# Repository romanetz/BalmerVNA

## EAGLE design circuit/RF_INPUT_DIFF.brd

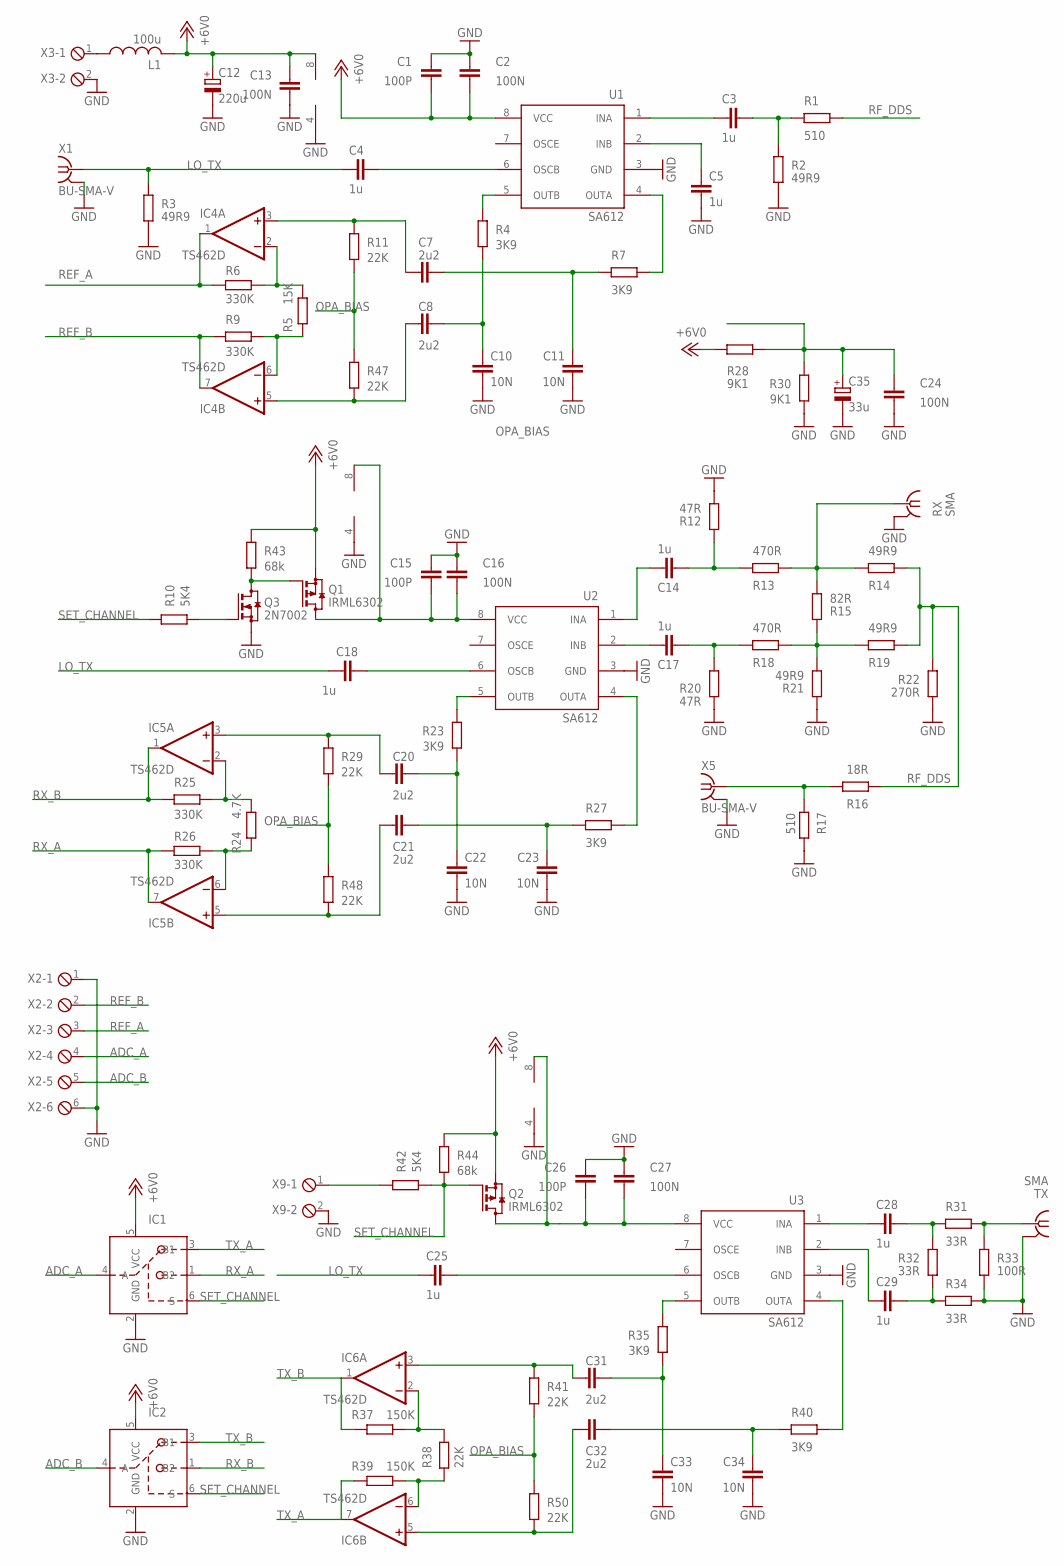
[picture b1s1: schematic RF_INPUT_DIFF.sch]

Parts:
C1, C15, C26: 100P; C0805
C2, C13, C16, C24, C27: 100N; C0603
C3, C5, C14, C17, C28, C29: 1u; C0603
C4, C18, C25: 1u; C0805
C7, C8, C20, C21, C31, C32: 2u2; C0805
C10, C11, C22, C23, C33, C34: 10N; C0805
C12: 220u; 153CLV-0605
C35: 33u; 153CLV-0605
IC1, IC2: SN74LVC1G3157DBVR; SOT23-6
IC4, IC5, IC6: TS462D; SO08
L1: 100u; 0207/12
Q1, Q2: IRML6302; SOT23
Q3: 2N7002; SOT23
R1, R17: 510; R0603
R2, R3, R14, R19, R21: 49R9; R0805
R4, R7, R23, R27, R35, R40: 3K9; R0603
R5: 15K; R0603
R6, R9, R25, R26: 330K; R0603
R10, R42: 5K4; R0603
R11, R29, R38, R41, R47, R48, R50: 22K; R0603
R12, R20: 47R; R0603
R13, R18: 470R; R0603
R15: 82R; R0603
R16: 18R; R0603
R22: 270R; R0603
R24: 4.7K; R0603
R28, R30: 9K1; R0603
R31, R32, R34: 33R; R0603
R33: 100R; R0603
R37, R39: 150K; R0603
R43, R44: 68k; R0603
RX: SMA; J502-ND-142-0701-801/806
TX: SMA; J502-ND-142-0701-801/806
U1, U2, U3: SA612; SO8
X1, X5: BU-SMA-V
X2: MPT6; 6POL254
X3, X9: MPT2; 2POL254

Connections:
+6V0: C1.1, C2.1, C12.+, C13.1, IC1.5 (VCC), IC2.5 (VCC), IC4.8 (V+), L1.2, Q1.2 (S), Q2.2 (S), R28.2, R43.1, R44.1, U1.8 (VCC)
ADC_A: IC1.4 (A), X2.4
ADC_B: IC2.4 (A), X2.5
GND: C1.2, C2.2, C5.2, C10.2, C11.2, C12.-, C13.2, C15.2, C16.2, C22.2, C23.2, C24.1, C26.2, C27.2, C33.2, C34.2, C35.-, IC1.2 (GND), IC2.2 (GND), IC4.4 (V-), IC5.4 (V-), IC6.4 (V-), Q3.2 (S), R2.1, R3.2, R12.2, R17.2, R20.1, R21.1, R22.2, R30.2, R33.2, R34.1, RX.G@1 (2), RX.G@2 (2), RX.G@3 (2), RX.G@4 (2), TX.G@1 (2), TX.G@2 (2), TX.G@3 (2), TX.G@4 (2), U1.3 (GND), U2.3 (GND), U3.3 (GND), X1.2, X1.3 (2), X1.4 (2), X1.5 (2), X2.1, X2.6, X3.2, X5.2, X5.3 (2), X5.4 (2), X5.5 (2), X9.2
LO_TX: C4.1, C18.1, C25.1, R3.1, X1.1
unnamed: R15.1, R18.1, R19.2, R21.2
unnamed: IC6.2 (-IN), R37.1, R38.1
unnamed: C25.2, U3.6 (OSCB)
unnamed: C26.1, C27.1, IC6.8 (V+), Q2.3 (D), U3.8 (VCC)
unnamed: R13.1, R14.2, R15.2, RX.1
unnamed: Q1.1 (G), Q3.3 (D), R43.2
unnamed: L1.1, X3.1
unnamed: C15.1, C16.1, IC5.8 (V+), Q1.3 (D), U2.8 (VCC)
unnamed: R42.1, X9.1
unnamed: IC4.2 (-IN), R5.1, R6.1
unnamed: C31.1, IC6.3 (+IN), R41.1
unnamed: C32.1, IC6.5 (+IN), R50.2
unnamed: IC4.6 (-IN), R5.2, R9.1
unnamed: Q3.1 (G), R10.2
unnamed: C7.1, IC4.3 (+IN), R11.1
unnamed: C8.1, IC4.5 (+IN), R47.2
unnamed: C20.1, IC5.3 (+IN), R29.1
unnamed: C21.1, IC5.5 (+IN), R48.2
unnamed: IC5.6 (-IN), R24.2, R26.1
unnamed: IC5.2 (-IN), R24.1, R25.1
unnamed: IC6.6 (-IN), R38.2, R39.1
unnamed: R31.1, R33.1, TX.1
unnamed: C28.2, R31.2, R32.1
unnamed: C29.2, R32.2, R34.2
unnamed: C29.1, U3.2 (INB)
unnamed: C28.1, U3.1 (INA)
unnamed: C31.2, C33.1, R35.2
unnamed: R40.1, U3.4 (OUTA)
unnamed: C32.2, C34.1, R40.2
unnamed: R35.1, U3.5 (OUTB)
unnamed: C17.1, U2.2 (INB)
unnamed: C17.2, R18.2, R20.2
unnamed: C14.1, U2.1 (INA)
unnamed: C20.2, C22.1, R23.2
unnamed: R27.1, U2.4 (OUTA)
unnamed: C21.2, C23.1, R27.2
unnamed: R23.1, U2.5 (OUTB)
unnamed: C14.2, R12.1, R13.2
unnamed: C18.2, U2.6 (OSCB)
unnamed: C5.1, U1.2 (INB)
unnamed: R14.1, R16.2, R19.1, R22.1
unnamed: C3.1, U1.1 (INA)
unnamed: C8.2, C10.1, R4.2
unnamed: R7.1, U1.4 (OUTA)
unnamed: C7.2, C11.1, R7.2
unnamed: R4.1, U1.5 (OUTB)
unnamed: C3.2, R1.2, R2.2
unnamed: C4.2, U1.6 (OSCB)
OPA_BIAS: C24.2, C35.+, R11.2, R28.1, R29.2, R30.1, R41.2, R47.1, R48.1, R50.1
REF_A: IC4.1 (OUT), R6.2, X2.3
REF_B: IC4.7 (OUT), R9.2, X2.2
RF_DDS: R1.1, R16.1, R17.1, X5.1
RX_A: IC1.1 (B2), IC5.7 (OUT), R26.2
RX_B: IC2.1 (B2), IC5.1 (OUT), R25.2
SET_CHANNEL: IC1.6 (S), IC2.6 (S), Q2.1 (G), R10.1, R42.2, R44.2
TX_A: IC1.3 (B1), IC6.7 (OUT), R39.2
TX_B: IC2.3 (B1), IC6.1 (OUT), R37.2

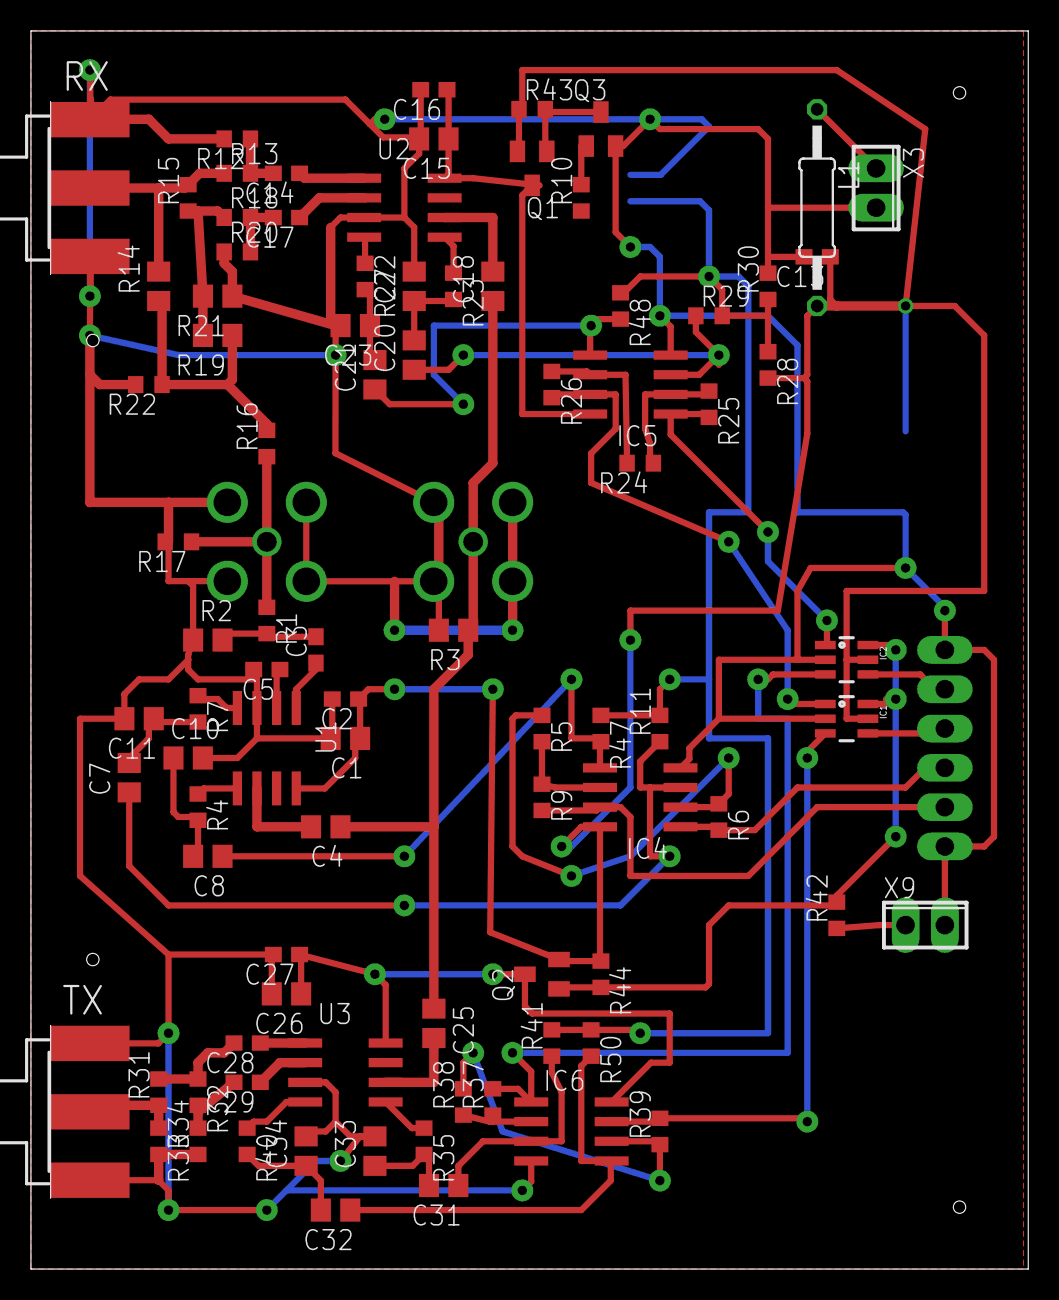
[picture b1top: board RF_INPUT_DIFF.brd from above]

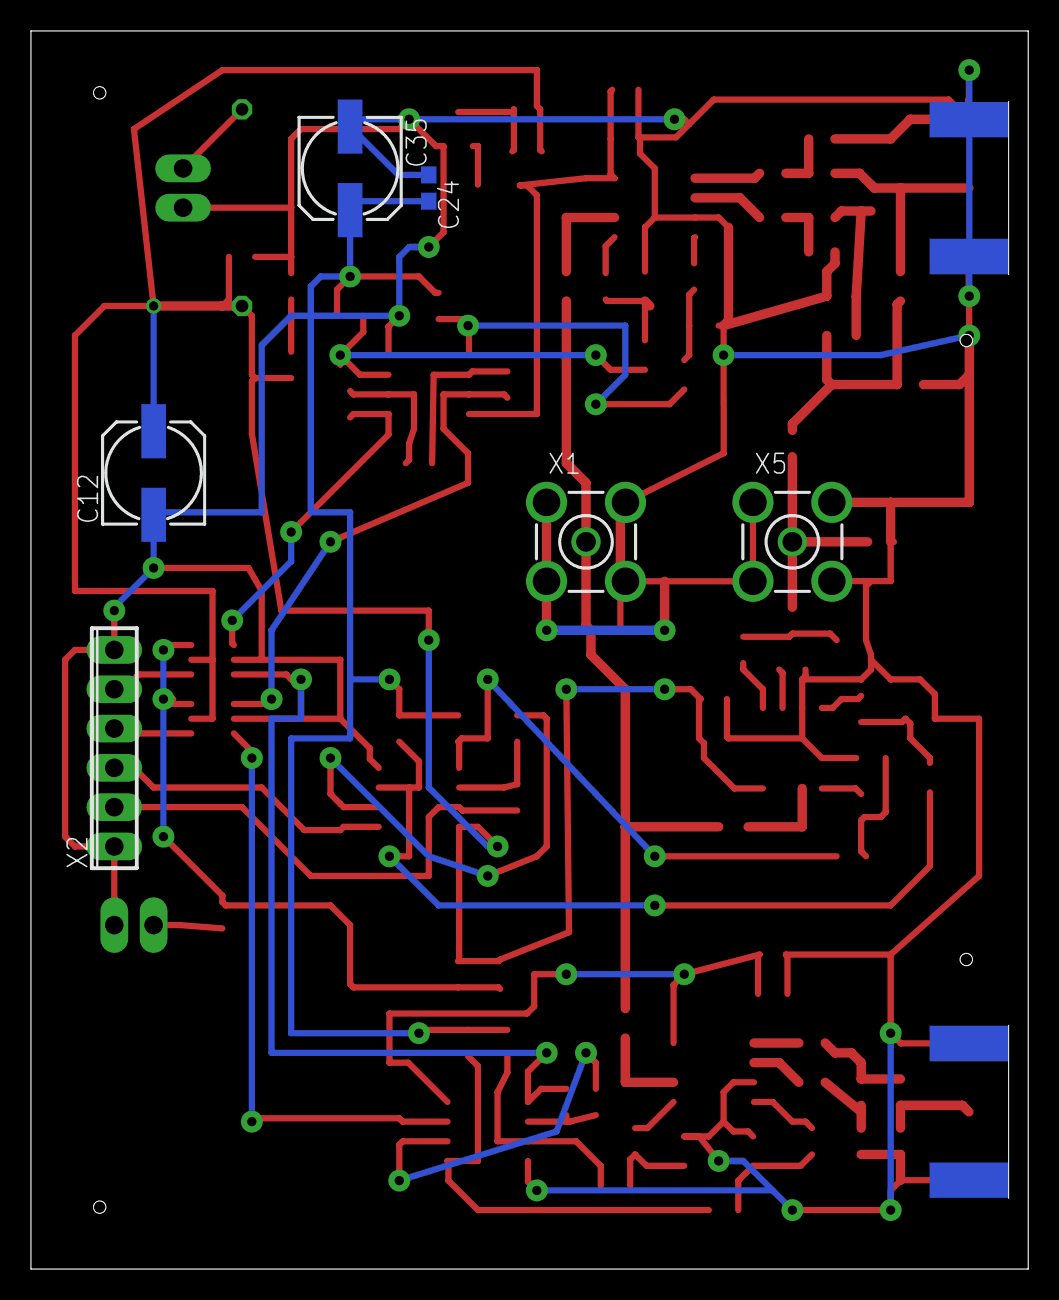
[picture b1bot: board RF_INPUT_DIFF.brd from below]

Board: 2 copper layers, 64.4 x 80.0 mm, 95 parts (6 on the bottom side), 62 nets.

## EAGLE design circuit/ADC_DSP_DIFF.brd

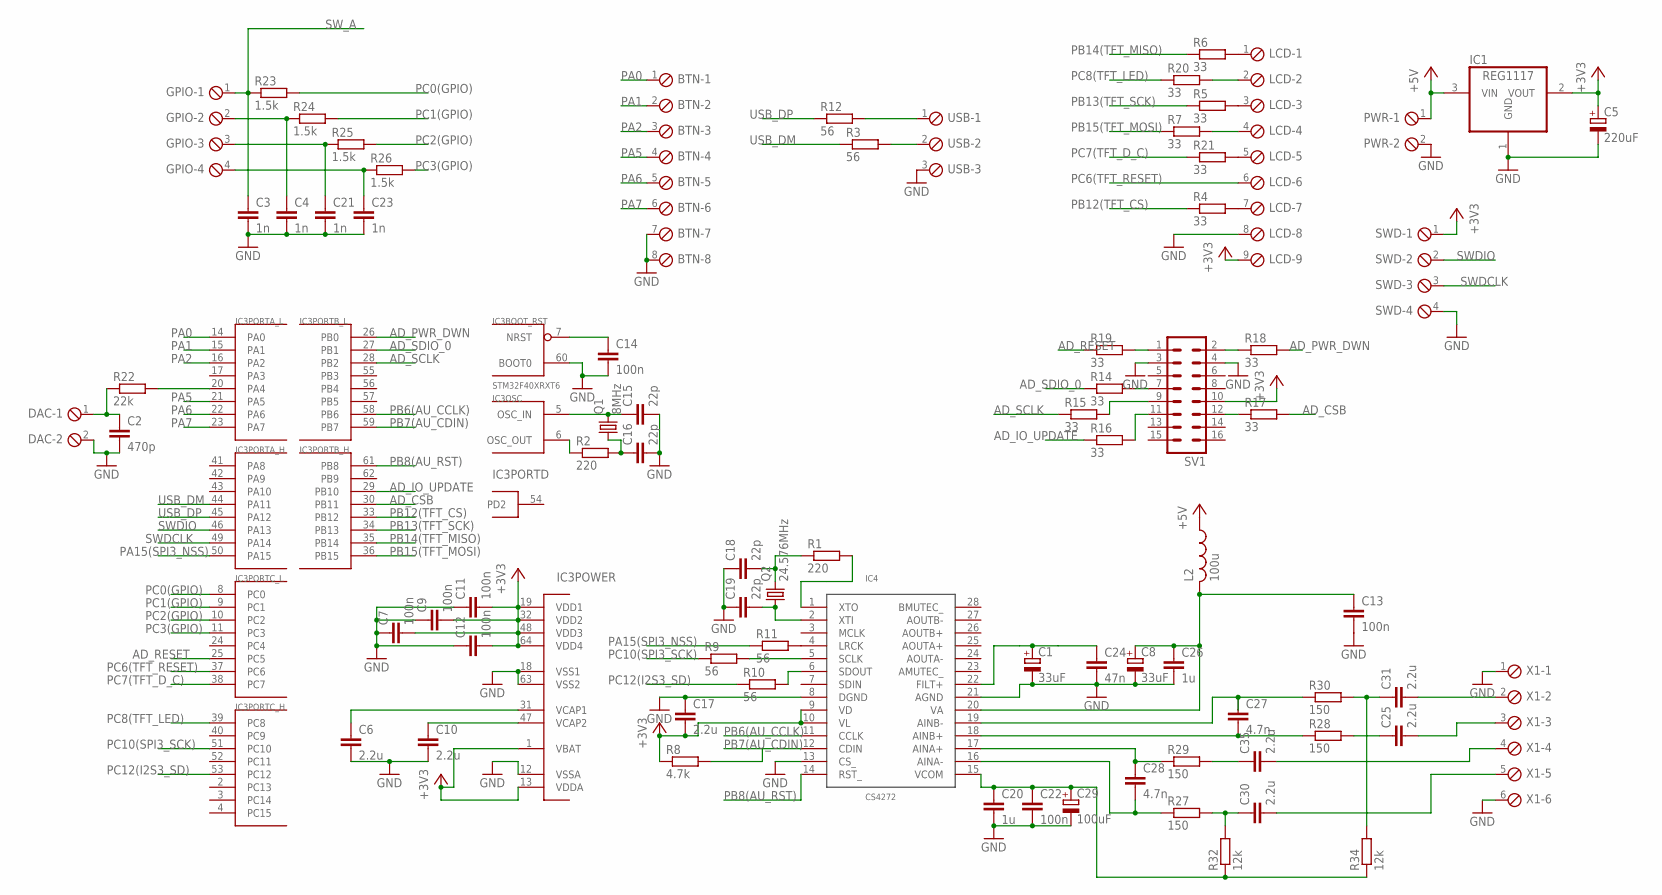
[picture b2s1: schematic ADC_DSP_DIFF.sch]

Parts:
BTN: MPT8; 8POL254
C1, C8: 33uF; 153CLV-0605
C2: 470p; C0805
C3, C4, C21, C23: 1n; C0805
C5: 220uF; 153CLV-0605
C6, C10, C17: 2.2u; C0603
C7, C9, C11, C12, C13, C14, C22: 100n; C0603
C15, C16, C18, C19: 22p; C0603
C20, C26: 1u; C0603
C24: 47n; C0805
C25, C30, C31, C35: 2.2u; C0805
C27, C28: 4.7n; C0805
C29: 100uF; 153CLV-0605
DAC: MPT2; 2POL254
GPIO: MPT4; 4POL254
IC1: REG1117; SOT223
IC3: STM32F40XRXT6; TQFP64
IC4: CS4272; TSSOP28
L2: 100u; 0207/12
LCD: MPT9; 9POL254
PWR: MPT2; 2POL254
Q1: 8MHz; HC49/S
Q2: 24.576MHz; HC49/S
R1, R2: 220; R0603
R3, R9, R10, R11, R12: 56; R0603
R4, R5, R6, R7, R14, R15, R16, R17, R18, R19, R20, R21: 33; R0603
R8: 4.7k; R0603
R22: 22k; R0603
R23, R24, R25, R26: 1.5k; R0603
R27, R28, R29, R30: 150; R0603
R32, R34: 12k; R0603
SV1: ML16
SWD: MPT4; 4POL254
USB: MPT3; 3POL254
X1: MPT6; 6POL254

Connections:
4052_B: C4.1, GPIO.2, R24.1
+3V3: C5.+, C7.2, C9.2, C11.2, C12.2, C17.2, IC1.2 (VOUT), IC3.1 (VBAT), IC3.13 (VDDA), IC3.19 (VDD1), IC3.32 (VDD2), IC3.48 (VDD3), IC3.64 (VDD4), IC4.9 (VD), IC4.10 (VL), LCD.9, R8.1, SV1.10, SWD.1
+5V: IC1.3 (VIN), L2.1, PWR.1
AD_CSB: IC3.30 (PB11), R17.2
AD_IO_UPDATE: IC3.29 (PB10), R16.1
AD_PWR_DWN: IC3.26 (PB0), R18.2
AD_RESET: IC3.25 (PC5), R19.1
AD_SCLK: IC3.28 (PB2), R15.1
AD_SDIO_0: IC3.27 (PB1), R14.1
AINB+: C27.2, IC4.18 (AINB+), R28.1
AVCC: C8.+, C13.1, C26.1, IC4.20 (VA), L2.2
D+: R12.2, USB.1
D-: R3.2, USB.2
GND: BTN.7, BTN.8, C1.-, C2.2, C3.2, C4.2, C5.-, C6.2, C7.1, C8.-, C9.1, C10.2, C11.1, C12.1, C13.2, C14.2, C15.2, C16.2, C17.1, C18.1, C19.1, C20.2, C21.2, C22.2, C23.2, C24.2, C26.2, C29.-, DAC.2, IC1.1 (GND), IC3.12 (VSSA), IC3.18 (VSS1), IC3.60 (BOOT0), IC3.63 (VSS2), IC4.8 (DGND), IC4.13 (CS_), IC4.21 (AGND), LCD.8, PWR.2, SV1.3, SV1.4, SWD.4, USB.3, X1.1, X1.6
unnamed: C10.1, IC3.47 (VCAP2)
unnamed: C6.1, IC3.31 (VCAP1)
unnamed: R16.2, SV1.11
unnamed: C14.1, IC3.7 (NRST)
unnamed: C15.1, IC3.5 (OSC_IN), Q1.2
unnamed: C16.1, Q1.1, R2.2
unnamed: C19.2, IC4.2 (XTI), Q2.1
unnamed: C18.2, Q2.2, R1.1
unnamed: IC4.4 (LRCK), R11.2
unnamed: IC4.5 (SCLK), R9.2
unnamed: IC4.6 (SDOUT), R10.2
unnamed: C1.+, C24.1, IC4.22 (FILT+)
unnamed: C27.1, IC4.19 (AINB-), R30.1
unnamed: R14.2, SV1.7
unnamed: C35.2, X1.4
unnamed: R19.2, SV1.1
unnamed: IC4.1 (XTO), R1.2
unnamed: C28.1, IC4.17 (AINA+), R29.1
unnamed: IC3.6 (OSC_OUT), R2.1
unnamed: LCD.1, R6.2
unnamed: LCD.3, R5.2
unnamed: LCD.2, R20.2
unnamed: R15.2, SV1.9
unnamed: LCD.4, R7.2
unnamed: C28.2, IC4.16 (AINA-), R27.1
unnamed: R18.1, SV1.2
unnamed: C31.1, R30.2, R34.2
unnamed: R17.1, SV1.12
unnamed: LCD.7, R4.2
unnamed: LCD.5, R21.2
unnamed: IC3.20 (PA4), R22.2
unnamed: C2.1, DAC.1, R22.1
unnamed: C30.1, R27.2, R32.2
unnamed: C25.1, R28.2
unnamed: C21.1, GPIO.3, R25.1
unnamed: C23.1, GPIO.4, R26.1
unnamed: C31.2, X1.2
unnamed: C35.1, R29.2
unnamed: C25.2, X1.3
unnamed: C30.2, X1.5
PA0: BTN.1, IC3.14 (PA0)
PA1: BTN.2, IC3.15 (PA1)
PA2: BTN.3, IC3.16 (PA2)
PA5: BTN.4, IC3.21 (PA5)
PA6: BTN.5, IC3.22 (PA6)
PA7: BTN.6, IC3.23 (PA7)
PA15(SPI3_NSS): IC3.50 (PA15), R11.1
PB6(AU_CCLK): IC3.58 (PB6), IC4.11 (CCLK)
PB7(AU_CDIN): IC3.59 (PB7), IC4.12 (CDIN), R8.2
PB8(AU_RST): IC3.61 (PB8), IC4.14 (RST_)
PB12(TFT_CS): IC3.33 (PB12), R4.1
PB13(TFT_SCK): IC3.34 (PB13), R5.1
PB14(TFT_MISO): IC3.35 (PB14), R6.1
PB15(TFT_MOSI): IC3.36 (PB15), R7.1
PC0(GPIO): IC3.8 (PC0), R23.2
PC1(GPIO): IC3.9 (PC1), R24.2
PC2(GPIO): IC3.10 (PC2), R25.2
PC3(GPIO): IC3.11 (PC3), R26.2
PC6(TFT_RESET): IC3.37 (PC6), LCD.6
PC7(TFT_D_C): IC3.38 (PC7), R21.1
PC8(TFT_LED): IC3.39 (PC8), R20.1
PC10(SPI3_SCK): IC3.51 (PC10), R9.1
PC12(I2S3_SD): IC3.53 (PC12), R10.1
SWDCLK: IC3.49 (PA14), SWD.3
SWDIO: IC3.46 (PA13), SWD.2
SW_A: C3.1, GPIO.1, R23.1
USB_DM: IC3.44 (PA11), R3.1
USB_DP: IC3.45 (PA12), R12.1
VCOM: C20.1, C22.1, C29.+, IC4.15 (VCOM), R32.1, R34.1

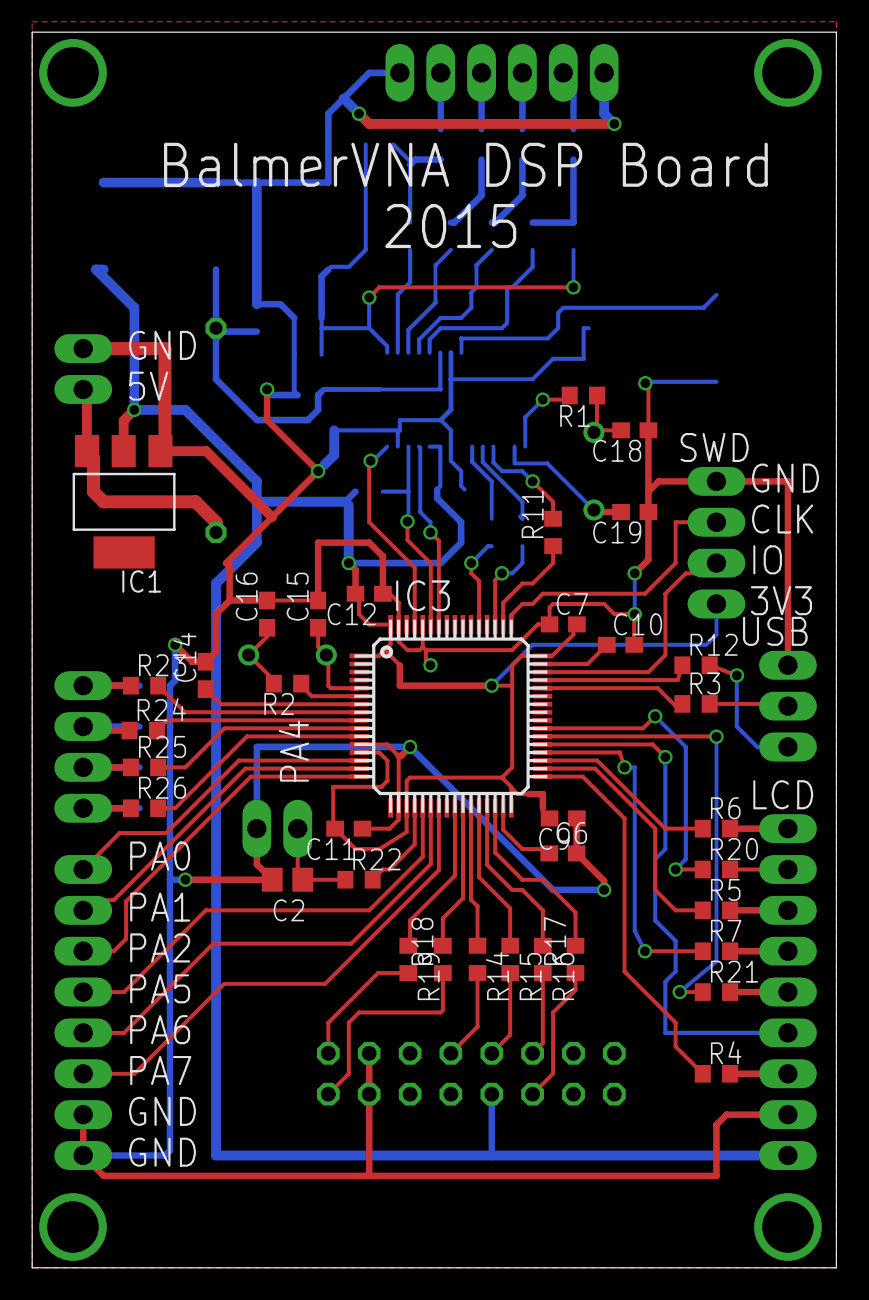
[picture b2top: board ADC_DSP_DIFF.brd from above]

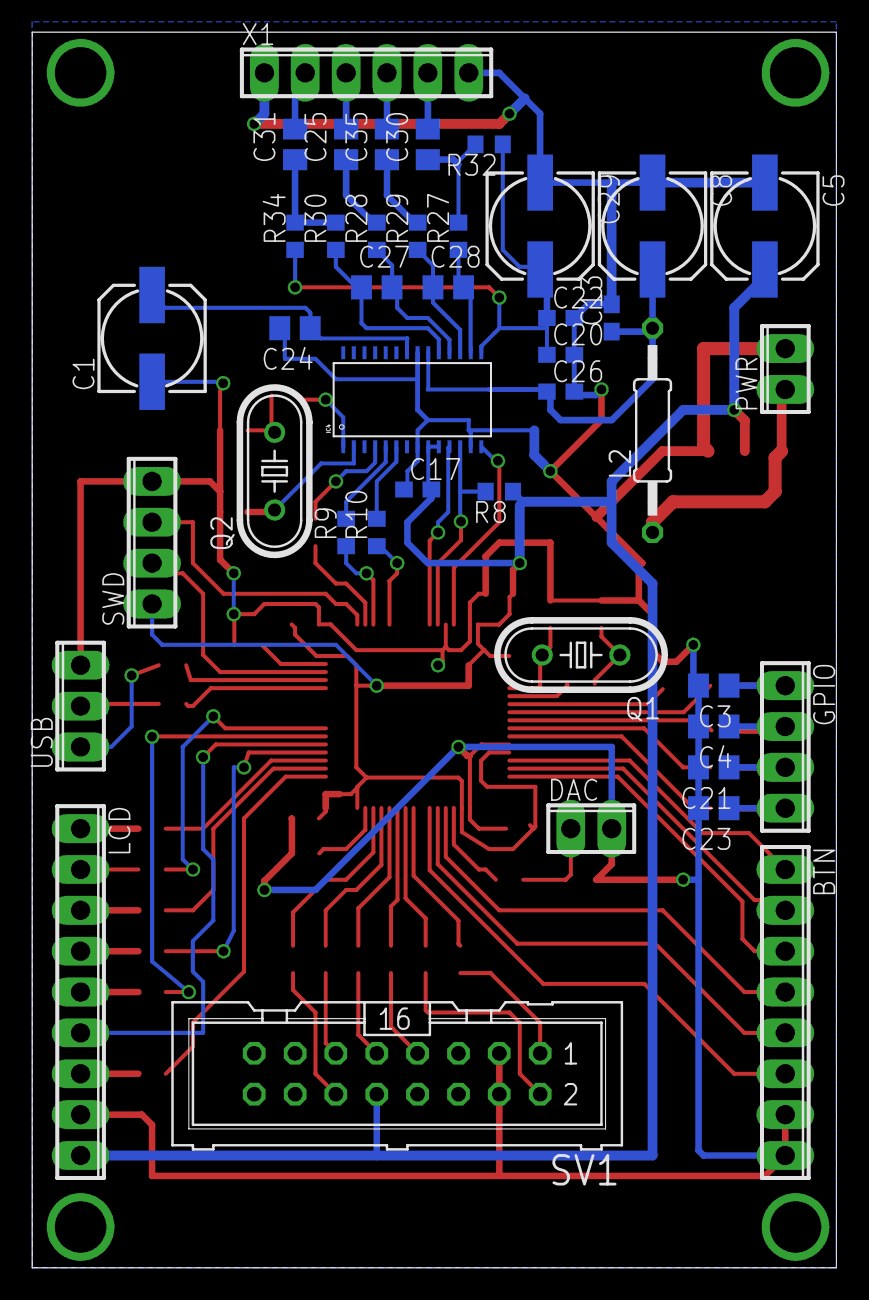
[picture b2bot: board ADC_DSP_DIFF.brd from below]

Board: 2 copper layers, 50.0 x 76.8 mm, 78 parts (42 on the bottom side), 83 nets.

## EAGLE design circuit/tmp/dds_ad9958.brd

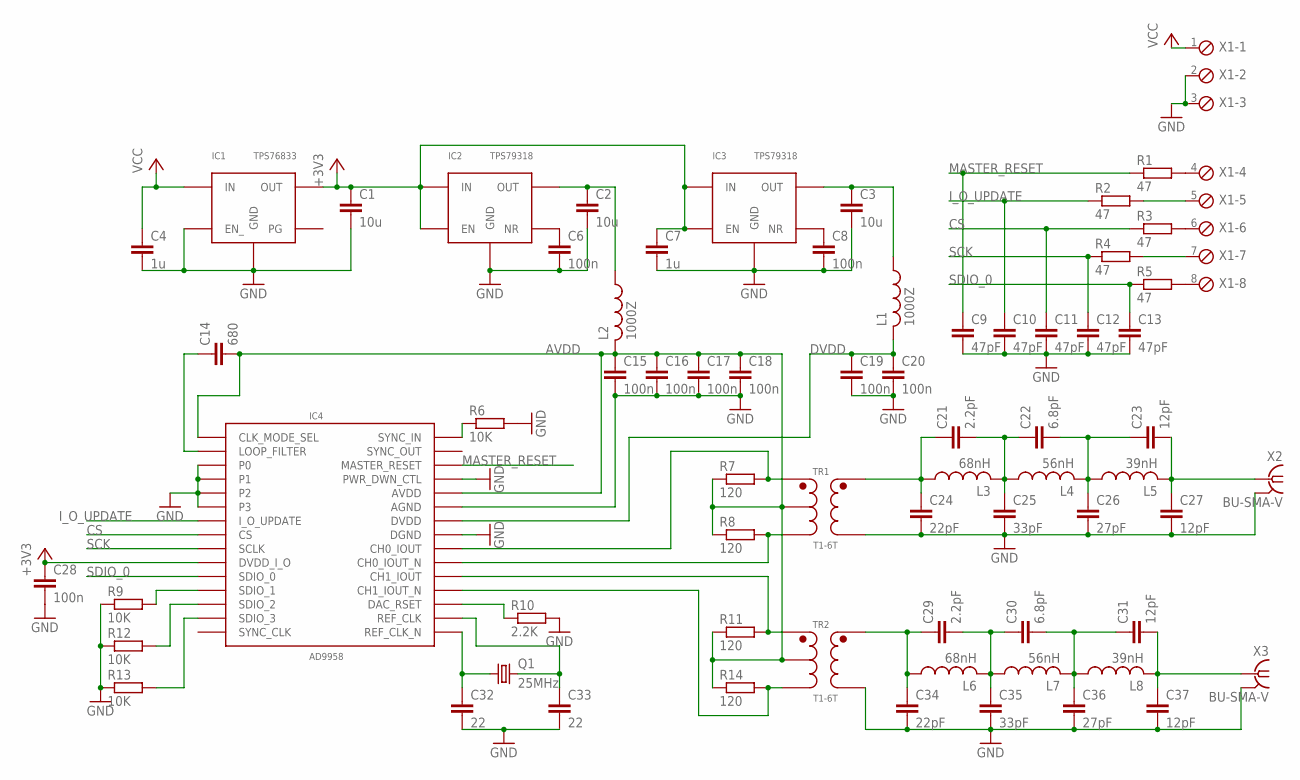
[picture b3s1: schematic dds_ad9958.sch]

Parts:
C1, C2, C3: 10u; C0805
C4, C7: 1u; C0603
C6, C8, C15, C16, C17, C18, C19, C20, C28: 100n; C0603
C9, C10, C11, C12, C13: 47pF; C0805
C14: 680; C0805
C21, C29: 2.2pF; C0805
C22, C30: 6.8pF; C0805
C23, C27, C31, C37: 12pF; C0805
C24, C34: 22pF; C0805
C25, C35: 33pF; C0805
C26, C36: 27pF; C0805
C32, C33: 22; C0603
IC1: TPS76833; SO8
IC2, IC3: TPS79318; SOT23-5
IC4: AD9958; CP-56-1
L1, L2: 1000Z; C0805
L3, L6: 68nH; C0805
L4, L7: 56nH; C0805
L5, L8: 39nH; C0805
Q1: 25MHz; HC49/S
R1, R2, R3, R4, R5: 47; R0603
R6, R9, R12, R13: 10K; R0603
R7, R8, R11, R14: 120; R0603
R10: 2.2K; R0603
TR1, TR2: T1-6T; KK81
X1: MPT8; 8POL254
X2, X3: BU-SMA-V

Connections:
+3V3: C1.1, C7.1, C28.1, IC1.5 (OUT), IC1.6 (OUT), IC2.1 (IN), IC2.3 (EN), IC3.1 (IN), IC3.3 (EN), IC4.P$49 (DVDD_I_O)
AVDD: C14.2, C15.1, C16.1, C17.1, C18.1, IC4.P$5 (AVDD), IC4.P$7 (AVDD), IC4.P$11 (AVDD), IC4.P$15 (AVDD), IC4.P$19 (AVDD), IC4.P$21 (AVDD), IC4.P$24 (CLK_MODE_SEL), IC4.P$26 (AVDD), IC4.P$29 (AVDD), IC4.P$30 (AVDD), IC4.P$31 (AVDD), IC4.P$33 (AVDD), IC4.P$35 (AVDD), IC4.P$36 (AVDD), IC4.P$37 (AVDD), IC4.P$39 (AVDD), L2.2, R7.1, R8.1, R11.1, R14.1, TR1.P$2 (SEC_CT), TR2.P$2 (SEC_CT)
CS: C11.1, IC4.P$47 (CS), R3.1
DVDD: C19.1, C20.1, IC4.P$45 (DVDD), IC4.P$55 (DVDD), L1.2
GND: C1.2, C2.2, C3.2, C4.2, C6.2, C7.2, C8.2, C9.2, C10.2, C11.2, C12.2, C13.2, C15.2, C16.2, C17.2, C18.2, C19.2, C20.2, C24.2, C25.2, C26.2, C27.2, C28.2, C32.2, C33.2, C34.2, C35.2, C36.2, C37.2, IC1.1 (GND), IC1.2 (EN_), IC2.2 (GND), IC3.2 (GND), IC4.P$4 (PWR_DWN_CTL), IC4.P$6 (AGND), IC4.P$10 (AGND), IC4.P$12 (AGND), IC4.P$16 (AGND), IC4.P$18 (AGND), IC4.P$20 (AGND), IC4.P$25 (AGND), IC4.P$40 (P0), IC4.P$41 (P1), IC4.P$42 (P2), IC4.P$43 (P3), IC4.P$44 (DGND), IC4.P$56 (DGND), IC4.PAD (AGND), R6.2, R9.1, R10.2, R12.1, R13.1, TR1.P$6 (PRI), TR2.P$6 (PRI), X1.2, X1.3, X2.2, X2.3 (2), X2.4 (2), X2.5 (2), X3.2, X3.3 (2), X3.4 (2), X3.5 (2)
I_O_UPDATE: C10.1, IC4.P$46 (I_O_UPDATE), R2.1
MASTER_RESET: C9.1, IC4.P$3 (MASTER_RESET), R1.1
unnamed: C32.1, IC4.P$22 (REF_CLK_N), Q1.1
unnamed: C21.1, C24.1, L3.1, TR1.P$4 (PRI_DOT)
unnamed: IC4.P$8 (CH0_IOUT), R7.2, TR1.P$3 (SEC_DOT)
unnamed: C6.1, IC2.4 (NR)
unnamed: C8.1, IC3.4 (NR)
unnamed: C2.1, IC2.5 (OUT), L2.1
unnamed: IC4.P$9 (CH0_IOUT_N), R8.2, TR1.P$1 (SEC)
unnamed: C3.1, IC3.5 (OUT), L1.1
unnamed: IC4.P$13 (CH1_IOUT), R11.2, TR2.P$3 (SEC_DOT)
unnamed: IC4.P$14 (CH1_IOUT_N), R14.2, TR2.P$1 (SEC)
unnamed: C21.2, C22.1, C25.1, L3.2, L4.1
unnamed: IC4.P$17 (DAC_RSET), R10.1
unnamed: IC4.P$1 (SYNC_IN), R6.1
unnamed: C14.1, IC4.P$27 (LOOP_FILTER)
unnamed: C33.1, IC4.P$23 (REF_CLK), Q1.2
unnamed: C22.2, C23.1, C26.1, L4.2, L5.1
unnamed: C23.2, C27.1, L5.2, X2.1
unnamed: C29.1, C34.1, L6.1, TR2.P$4 (PRI_DOT)
unnamed: C29.2, C30.1, C35.1, L6.2, L7.1
unnamed: C30.2, C31.1, C36.1, L7.2, L8.1
unnamed: C31.2, C37.1, L8.2, X3.1
unnamed: R3.2, X1.6
unnamed: R5.2, X1.8
unnamed: R1.2, X1.4
unnamed: R2.2, X1.5
unnamed: R4.2, X1.7
SCK: C12.1, IC4.P$48 (SCLK), R4.1
SDIO_0: C13.1, IC4.P$50 (SDIO_0), R5.1
SDIO_1: IC4.P$51 (SDIO_1), R9.2
SDIO_2: IC4.P$52 (SDIO_2), R12.2
SDIO_3: IC4.P$53 (SDIO_3), R13.2
VCC: C4.1, IC1.3 (IN), IC1.4 (IN), X1.1

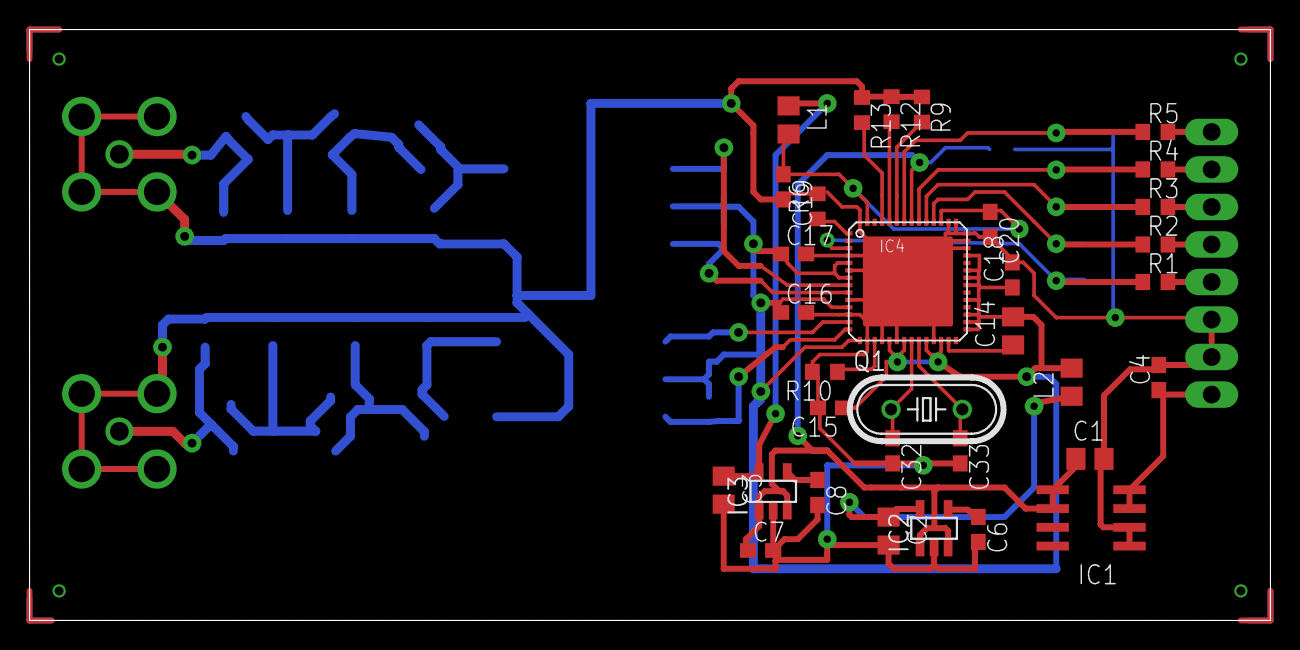
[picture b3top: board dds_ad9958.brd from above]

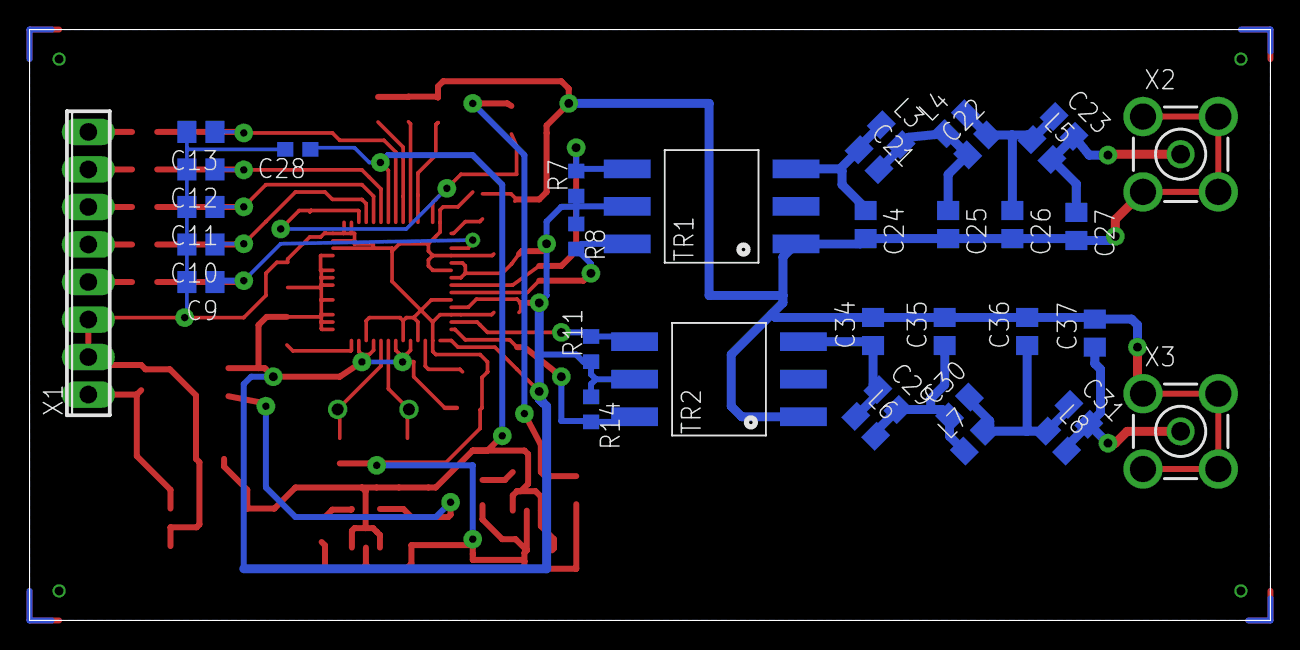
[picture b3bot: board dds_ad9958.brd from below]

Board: 2 copper layers, 84.0 x 40.0 mm, 68 parts (35 on the bottom side), 39 nets.

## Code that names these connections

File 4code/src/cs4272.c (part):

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#include "delay.h"
#include "process_sound.h"

//	CCLK - PB6
//	CDIN - PB7
//  RST - PB8

// SPI3_NSS PA15
// SPI3_SCK PC10
// I2S3_SD  PC12



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	/* setup SCL and SDA pins
	 * You can connect I2C1 to two different
	 * pairs of pins:
	 * 1. SCL on PB6 and SDA on PB7
	 * 2. SCL on PB8 and SDA on PB9
	 */
	GPIO_InitStruct.GPIO_Pin = GPIO_Pin_6 | GPIO_Pin_7; // we are going to use PB6 and PB7
	GPIO_InitStruct.GPIO_Mode = GPIO_Mode_AF;			// set pins to alternate function
	GPIO_InitStruct.GPIO_Speed = GPIO_Speed_2MHz;//GPIO_Speed_50MHz;		// set GPIO speed
	GPIO_InitStruct.GPIO_OType = GPIO_OType_OD;			// set output to open drain --> the line has to be only pulled low, not driven high
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	I2S_InitTypeDef I2S_InitStruct;

	//I2S3 used
	//PA15 - NSS
	//PC10 - SCK
	//PC12 - MOSI
	RCC_APB1PeriphClockCmd(RCC_APB1Periph_SPI3, ENABLE);
	RCC_AHB1PeriphClockCmd(RCC_AHB1Periph_DMA1, ENABLE);
	RCC_AHB1PeriphClockCmd(RCC_AHB1Periph_GPIOA|RCC_AHB1Periph_GPIOC, ENABLE);
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
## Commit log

2015-02-14 - пытается сделать DSP плату, в которой будут все необходимые выводы
2015-02-15 - добавили LCD разъем
2015-02-15 - добавил 4 GPIO
2015-02-15 - развели еще немного
2015-02-15 - развели в первом приближении
2015-02-16 - развели вход для CS4272
2015-02-18 - перед заменой на более быстрый мультиплексор.
2015-02-18 - перержавел по халявному под SN74LVC1G3157DBVR
2015-02-18 - более -менее разведенная плата
2015-02-19 - уменьшили ширину платы
2015-02-21 - плата, которую будем травить
2015-02-21 - один из проводов пересекался с другим
2015-02-24 - код выводящий данные на дисплей
2015-03-01 - работающий DDS
2015-03-02 - довели до состояния "рабочая звуковая"
2015-03-07 - была ошибка в TimeMs() - конденсатор 100 uF на VCOM - не успевает выводить на дисплей и обрабатывать звук.
2015-03-09 - начали делать высокочастотную входную часть
2015-03-09 - развели половину
2015-03-09 - почти разведенная схема
2015-03-11 - добавили транзистор, чтобы переключалось одной линией. - индуктивность на питание
2015-03-12 - немного компактифицировали
2015-03-13 - развели вчерновую
2015-03-13 - вроде готовая плата
2015-03-15 - то что напечатаем
2015-03-31 - работающий в первом приближении USB Virtual Com Port
2015-04-03 - отсылаем/принимаем данные - скрипт для python3.4
2015-04-03 - посылаем и принимаем большие пачки данных
2015-04-05 - считываем синус с I/Q канала
2015-04-05 - графики похожие на правду!
2015-04-06 - переключение RX/TX
2015-04-07 - определяем частоту сигнала
2015-04-08 - убрали ошибку связанную с округлением, при установке частоты. Теперь ПЧmax - ПЧmin = 0.3 Hz (а раньше было 0.5 Hz)
2015-04-09 - вычисляем фазу и выводим на экран
2015-04-10 - метод Гауда для нашей системы уравнений - подредактировали ADC_DSP чтобы на одну страницу влезало
2015-04-12 - иногда на 1, а иногда на 2 байта ошибается при чтении из CS4272
2015-04-12 - говнокод, запускаем SPI/DMA раньше, чем CS4272. Для того, чтобы одинаковые данные приходили постоянно.
2015-04-12 sin -> sinf . Теперь код работает за разумное время
2015-04-13 - добавили пример AD9958 платки
2015-04-14 - быстрое сканирование диапазона, с расчетами на микроконтроллер
2015-05-16 - немного математики
2015-09-20 - начали рисовать платку с дифференциальным входом.
2015-09-21 - немного развели схему.
2015-09-24 - скомпилировали под Linux
2015-09-24 - проект для Qt Creator для удобного редактирования исходников.
2015-09-27 - send first command to vna from qt
2015-09-27 - отделили команды от девайса
    - добавили тулбар
    - проверили encode/decode на "big data"
2015-09-30 - немного работы с COM port
    - подключили QCustomPlot
2015-10-01 - вроде все линии переразвели
2015-10-03 - class VnaCommand, команды, которые можно добавлять в очередь.
2015-10-03 - последовательность команд, выполняемая асинхронно.
2015-10-03 - добавили VnaSamplingBufferSize
    - добавили возможность перезапустить команду
2015-10-03 - прочитали данные и запихнули на график.
2015-10-05 - добавили ring_buffer
    - добавили много команд
    - определили, что из-за того, что девайс определяется как ttyACMx ему посылаются AT команды
2015-10-06 - после того, как считали данные с девайса, показываем график.
2015-10-06 - combobox rx/tx
2015-10-08 - запустили команды COMMAND_GET_CALCULATED и COMMAND_START_SAMPLING_AND_CALCULATE
2015-10-09 - график успешно нарисовался по данным просчитанным железкой.
2015-10-11 - версия, которую будем отправлять на завод
2015-10-18 - пршем данные в xml
2015-10-18 - пишем данные в xml
2015-10-18 - читаем данные в python
2015-10-21 - add hardware wait before start sampling
2015-10-23 - немного расчетов
2015-10-23 - непонятная R1=50 всегда
2015-10-23 - все загадочнее и загадочнее, проверили все :)
2015-10-23 - нашли, где плюсик с минусиком был перепутан
2015-10-23 - несколько часов мучений, и графики vcc1 совпадают!
2015-10-24 - стандартные частоты для калибровки
2015-10-26 - open-short-load калибровка по Z
2015-10-28 - забытый calibration.py
2015-10-29 - мысли про tx канал
2015-10-29 - добавили калибровочные данные в хранилище
2015-10-30 - немного gitignore
2015-10-30 - удалили из репозиртория пользовательский файл.
2015-10-31 - начали делать вариант с дифференциальным выходом.
2015-10-31 - продолжили работу над diff входом
2015-11-01 - начали рисовать платку для diff выхода.
2015-11-02 - просто, чтобы совпададало с домашней версией.
2015-11-03 - TX выдает разумные данные!
2015-11-03 - последние изменения, просто для синхронизации
2015-11-04 - еще немного развели плату
2015-11-04 - начали калибровку по S параметрам
2015-11-05 - работающая calculateS11_S21 для случая подключения симметричного элемента между RX и TX
2015-11-08 - начали делать диалог выбора частоты.
2015-11-08 - диалог DialogSelectFrequency
